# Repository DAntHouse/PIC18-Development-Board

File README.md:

## PIC 18 USB Development Board

# Objective

This project is to help people learn PIC programming and Python programming. The board is designed with a FTDI chip to convert PC USB data into UART data. 

# Parts

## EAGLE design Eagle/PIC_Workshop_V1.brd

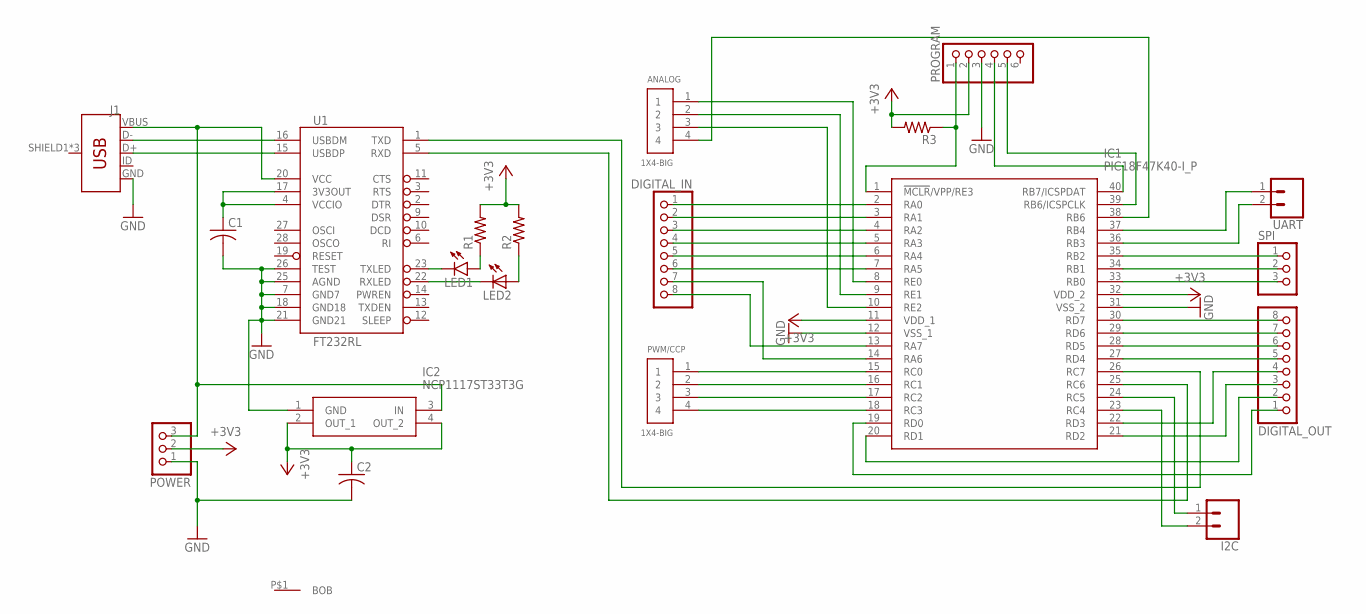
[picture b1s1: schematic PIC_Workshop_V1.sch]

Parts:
ANALOG: 1X4-BIG; 1X04-BIG
C1, C2: C-USC0805; C0805
DIGITAL_IN: PINHD-1X8BIG; 1X08-BIG
DIGITAL_OUT: PINHD-1X8BIG; 1X08-BIG
I2C: CONN_02; 1X02
IC1: PIC18F47K40-I_P; DIP1543W58P254L5175H635Q40N
IC2: NCP1117ST33T3G; SOT230P700X180-4N
J1: USB_MICRO-BREDUCED_PASTE; USB-B-MICRO-SMD_RED_PASTE
LED1: LED3MM
LED2: LEDCHIPLED_0603; CHIPLED_0603
POWER: PINHD-1X3; 1X03
PROGRAM: PINHD-1X6; 1X06
PWM/CCP: 1X4-BIG; 1X04-BIG
R1: R-US_0204/7; 0204/7
R2, R3: R-US_M0805; M0805
SPI: PINHD-1X3; 1X03
U1: FT232RL; SSOP28DB
U$1: BOBBOB; BOB
UART: CONN_02; 1X02

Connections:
+3V3: C2.1, IC1.11 (VDD_1), IC1.32 (VDD_2), IC2.2 (OUT_1), IC2.4 (OUT_2), POWER.2, PROGRAM.2, R1.2, R2.2, R3.2
GND: C1.2, C2.2, IC1.12 (VSS_1), IC1.31 (VSS_2), IC2.1 (GND), J1.GND, POWER.1, PROGRAM.3, U1.7 (GND7), U1.18 (GND18), U1.21 (GND21), U1.25 (AGND), U1.26 (TEST)
unnamed: J1.D-, U1.16 (USBDM)
unnamed: J1.D+, U1.15 (USBDP)
unnamed: IC1.1 (!MCLR!/VPP/RE3), PROGRAM.1, R3.1
unnamed: IC1.40 (RB7/ICSPDAT), PROGRAM.4
unnamed: IC1.39 (RB6/ICSPCLK), PROGRAM.5
unnamed: DIGITAL_OUT.8, IC1.30 (RD7)
unnamed: DIGITAL_OUT.7, IC1.29 (RD6)
unnamed: DIGITAL_OUT.6, IC1.28 (RD5)
unnamed: DIGITAL_OUT.5, IC1.27 (RD4)
unnamed: DIGITAL_OUT.4, IC1.22 (RD3)
unnamed: DIGITAL_OUT.3, IC1.21 (RD2)
unnamed: DIGITAL_OUT.2, IC1.20 (RD1)
unnamed: DIGITAL_OUT.1, IC1.19 (RD0)
unnamed: DIGITAL_IN.1, IC1.2 (RA0)
unnamed: DIGITAL_IN.2, IC1.3 (RA1)
unnamed: DIGITAL_IN.3, IC1.4 (RA2)
unnamed: DIGITAL_IN.4, IC1.5 (RA3)
unnamed: DIGITAL_IN.5, IC1.6 (RA4)
unnamed: DIGITAL_IN.6, IC1.7 (RA5)
unnamed: DIGITAL_IN.7, IC1.14 (RA6)
unnamed: DIGITAL_IN.8, IC1.13 (RA7)
unnamed: ANALOG.1, IC1.8 (RE0)
unnamed: ANALOG.2, IC1.9 (RE1)
unnamed: ANALOG.3, IC1.10 (RE2)
unnamed: IC1.26 (RC7), U1.1 (TXD)
unnamed: IC1.25 (RC6), U1.5 (RXD)
unnamed: IC1.15 (RC0), PWM/CCP.1
unnamed: IC1.16 (RC1), PWM/CCP.2
unnamed: IC1.17 (RC2), PWM/CCP.3
unnamed: IC1.18 (RC3), PWM/CCP.4
unnamed: IC1.33 (RB0), SPI.3
unnamed: IC1.34 (RB1), SPI.2
unnamed: IC1.35 (RB2), SPI.1
unnamed: I2C.2, IC1.23 (RC4)
unnamed: I2C.1, IC1.24 (RC5)
unnamed: IC1.36 (RB3), UART.2
unnamed: IC1.37 (RB4), UART.1
unnamed: ANALOG.4, IC1.38 (RB6)
unnamed: IC2.3 (IN), J1.VBUS, POWER.3, U1.20 (VCC)
unnamed: LED1.K (C), U1.23 (TXLED)
unnamed: LED2.C, U1.22 (RXLED)
unnamed: LED1.A, R1.1
unnamed: C1.1, U1.4 (VCCIO), U1.17 (3V3OUT)
unnamed: LED2.A, R2.1

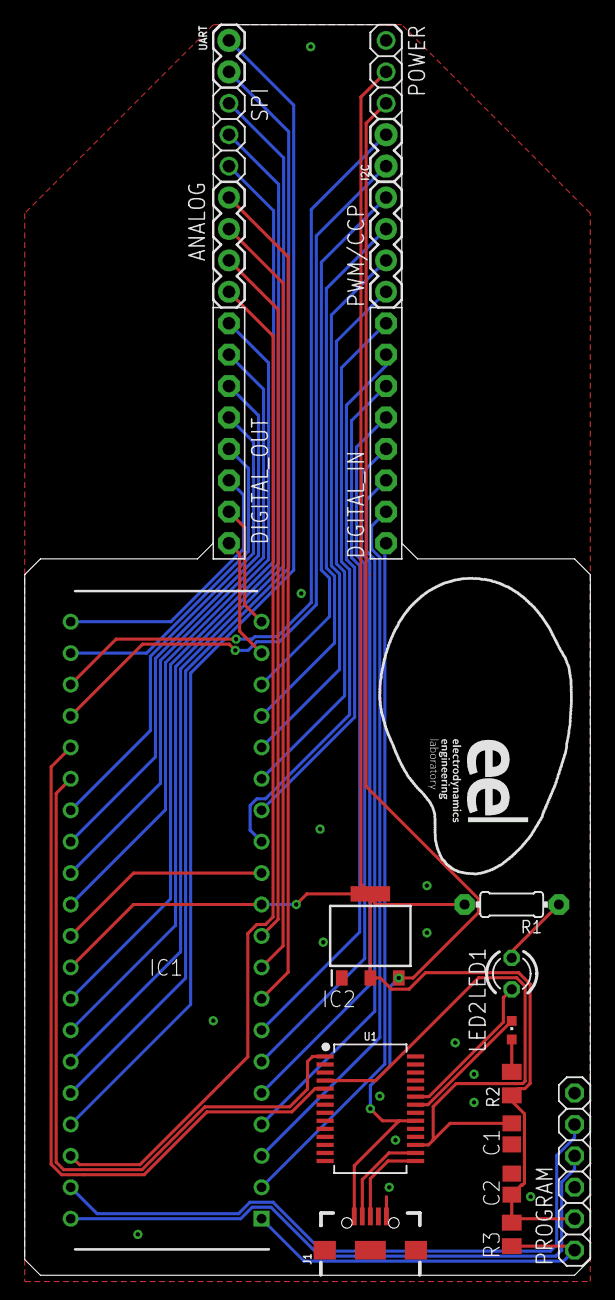
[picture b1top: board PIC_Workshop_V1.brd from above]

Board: 2 copper layers, 45.7 x 101.1 mm, 21 parts (0 on the bottom side), 46 nets.

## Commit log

2019-03-23 Set theme jekyll-theme-slate
2019-05-27 Create fol
2019-05-27 Rename PIC_Workshop_V1.brd to Eagle/PIC_Workshop_V1.brd
2019-05-27 Rename eagle.epf to Eagle/eagle.epf
2019-05-27 Create f

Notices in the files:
parts and their libraries:
SparkFun-Connectors: Licensing: Creative Commons ShareAlike 4.0 International - https://creativecommons.org/licenses/by-sa/4.0
